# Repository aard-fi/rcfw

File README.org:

* NoTankS Arduino firmware                                            :TOC_4:
  - [[#introduction][Introduction]]
    - [[#working-features][Working features]]
      - [[#general][General]]
      - [[#notanks][NoTankS]]
    - [[#building][Building]]
    - [[#planned-features][Planned features]]
      - [[#general-1][General]]
      - [[#notanks-1][NoTankS]]
    - [[#required-hardware][Required hardware]]
      - [[#flysky-hardware][Flysky hardware]]
      - [[#elrs-hardware][ELRS hardware]]
  - [[#modified-parts][Modified parts]]
  - [[#rc-hardware][RC hardware]]
    - [[#pistol-grip-elrs-transmitter][Pistol grip ELRS transmitter]]
    - [[#elrs-transmitter][ELRS transmitter]]
    - [[#flysky-transmitter][Flysky transmitter]]
    - [[#6-channel-receivers][6 channel receivers]]
  - [[#arduino-shield][Arduino shield]]
  - [[#manual-wiring][Manual wiring]]
    - [[#led-groups][LED groups]]
    - [[#elrs-receiver-reset][ELRS receiver reset]]
    - [[#models][Models]]
      - [[#arctic-tinyrider][Arctic Tinyrider]]
      - [[#notanks-2][NoTanks]]
      - [[#rc-benchy][RC Benchy]]
  - [[#transmitter-channels][Transmitter channels]]
    - [[#default-channel-mapping-for-radiomaster-mt12][Default channel mapping for Radiomaster MT12]]
    - [[#default-channel-mapping-for-radiomaster-pocket][Default channel mapping for Radiomaster Pocket]]
    - [[#default-channel-mapping-for-flysky-fs-i6][Default channel mapping for Flysky FS-i6]]

** Introduction

This is a variant of my [[https://github.com/bwachter/arctic_tinyrider][Arctic Tinyrider controller firmware]], trying to support multiple models (including the original one) with compile time switches:

- the [[https://www.printables.com/model/114300-arctic-tinyrider-rc-snowmobile][Arctic Tinyrider RC snowmobile]]
- the [[https://www.thingiverse.com/thing:2789361][NoTankS tank]]
- the [[https://www.printables.com/model/34128-rc-benchy][RC Benchy]]

It should also work without changes for any model either just using two motors, ore one motor and one servo for steering - the upcoming model specific details are mostly about LED effects.

You can download pre-built firmware for all supported hardware and feature combinations from the [[https://github.com/aard-fi/rcfw/releases][releases page]] and flash them with [[https://github.com/avrdudes/avrdude][avrdude]] (=avrdude -p atmega328p|atmega4809 -c arduino|jtag2updi -P /dev/ttyS0 -b 115200=) , or follow the build instructions below.

Currently supported are the [[https://store.arduino.cc/products/arduino-nano][Arduino Nano]] and the [[https://store.arduino.cc/products/arduino-nano-every][Arduino Nano Every]] as well as all their clones - especially for the Nano I'd recommend getting a cheap clone (ideally with USB-C) via ebay or aliexpress.

The Every uses the first UART via USB serial, and the second UART via the RX/TX pins (which are used for connecting to the receiver). The older Nano connects its first (and only) UART to both USB serial and the RX/TX pins - so it should be programmed with the rest of the circuit powered down.

This is mostly annoying when actively developing - so for models which only occasionally get updated firmware without active development a generic Nano clone should be sufficient, and way cheaper. At the time of writing a Nano clone (which even has USB C) costs less than 1 EUR, while the original Every goes up to 20 EUR, with clones (which also stick to Micro USB for some reason) selling for roughly 12 EUR. Schematics and PCB layout for a shield offering all connections used by this project are in ./arduino-nano-shield/ - and can be [[https://www.pcbway.com/project/shareproject/rcfw_Arduino_Nano_shield_ea388a65.html][ordered via PCBWay]]. See below for build instructions.

The only other disadvantage of the original Nano for basic models is the lower serial port speed of 115200 - but that should not be an issue for the type of model this firmware tries to support. For ELRS receivers you may have to set their serial speed to 115200 once when using a Nano.

*** Working features
The initial version was written for IBUS receivers - some of the advanced features may not work with CRSF receivers yet.

**** General
- ignition switch: throttle is pinned to zero unless ignition switch is on. This allows somewhat safer handling when not fully switched off. A LED connected to D13 will signal throttle state by blinking (off) or solid light (on).
- throttle and steering (obviously)
- reversing, when supported by the model
- control remapping: a three state switch can be used to change controls. Exact functionality depends on model and transmitter used.
- dynamic speed control: a dial can be used to limit the speed without having to change the throttle curve in the transmitter. In the default setting the transmitter starts with 50% output, and can be set up to 100%. Exact functionality depends on model and transmitter used.
- failsafe requires the ability of the receiver to send sane values when connectivity has been lost. This works well with ELRS receivers, untested with Flysky, though it may be possible with some.
- three groups of LEDs can be used for models in the standard configuration: back/power, front and effect. Any of those LED groups can be set to an arbitrary number of pins from 0 to as many pins are available

Ignition switching, control remapping and dynamic speed control currently can be disabled at compile time to free up channels.

Flysky support will mostly be maintained at the current level, while new features target CRSF. Some rely on ELRS/CRSF behaviour, while others could be enabled somewhat easily for flysky as well. CRSF only features are:

- link detection on startup. The main program will only start running once link has been established
- receiver power cycling. With additional wiring (see below) the receiver can be power cycled on startup. This is recommended, as ELRS receivers go into WiFi configuration mode after some time, and would need manual intervention
- link monitoring with board reset after timeout, configurable at compile time
- remote type detection. With the controls for channel 4 in default position the type of remote (stick or pistol grip) can be auto-detected. This is a compile time setting, which defaults to on.

**** NoTankS
- turning based on accelerating or decelerating one side, depending on the current speed. This also allows turning at zero speed
- curves for low speed cutoff to keep the motors cooler

*** Building

Get the [[https://www.arduino.cc/en/software][Arduino IDE]], and the following libraries:

- the [[https://github.com/arduino-libraries/Servo][servo library]]
- for CRSF use [[https://github.com/AlfredoSystems/AlfredoCRSF][AlfredoCRSF]]
- for IBUS use [[https://github.com/bmellink/IBusBM][IBusBM]]

Configure the correct board (Nano or Nano Every are supported, Every recommended), and go through the defines at the beginning of the file to configure the build for your model and transmitter setup.

Alternatively you can install [[https://docs.arduino.cc/arduino-cli/][arduino-cli]], and use the included Makefile: =make deps= once, and then =make all-variants=, or =make= with the flags you want. See the Makefile for more details.

*** Planned features
**** General
- steering curve adjustment for controllers with two potis
- toggling ESC power supply/board power supply

**** NoTankS
- optimising the steering to result in as little speed change as possible

*** Required hardware

- one Arduino Nano Every
- one receiver
- one radio
- two ESCs with reverse which use the first PWM input value to configure the zero position. It also should be configurable for forward/reverse - most come in forward/reverse/brake configuration, and not all allow omitting the brake. I'm using the 160A variant from [[https://www.aliexpress.com/item/1005006256842555.html][here]].

**** Flysky hardware

Recommendation here is the FS-A8S as receiver, and an AFHDS 2a transmitter, like the FS-i6. When starting new I'd recommend going for ELRS hardware instead, though.

The main drawback of the FS-A8S is the lack of a second iBus - so we can't send custom telemetry data back to the radio. On the plus side it is a tiny receiver, very cheap (roughly 10 EUR), and can output up to 18 channels via iBus. I'm not aware of receivers of a similar size with more than one iBus - other small Flysky receivers just have more connectors for PWM breakout cables, which we don't need as we're controlling that part via the Arduino.

**** ELRS hardware

Any ELRS transmitter should do, if you're looking for recommendations:

- for a pistol grip style one, Radiomaster MT12
- for a traditional drone/plane one, Radiomaster Boxer M2, or if you want to be fancier, the TX16S
- for a small, more portable one, Radiomaster Pocket

For receivers any of the compact (nano) receivers should be fine, from any manufacturer - as far as I'm aware all of them have RX/TX ports for CRSF. Some of the larger ones do not have that - but the tiny ones are easier to stuff into models anyway.

Main drawbock of ELRS is that the receivers are roughly double the price of AFHDS ones - but for that we always have the ability to send telemetry back.

** Modified parts
For some of the models I've modified parts. You can find those in separate repositories:

- [[https://github.com/bwachter/arctic_tinyrider][Arctic Tinyrider]]
- [[https://github.com/bwachter/notanks/][NoTankS]]

** RC hardware

Both throttle curve and trim settings will change the values sent by the transmitter. Currently the assumption is that for our models we can adjust those settings on the Arduino, so adjusted input may be improperly handled - don't use that.

*** Pistol grip ELRS transmitter
With the default setup of steering at channel 1 and throttle at channel two basic control will work out of the box.

Remapping of throttle and steering is not supported as it does not make much sense with that style of transmitter.

The ignition switch is expected on channel 9.

*** ELRS transmitter
This setup is currently untested, but should be working.

The ignition switch is expected on channel 5, which should be one of the two-state switches in the default configuration.

*** Flysky transmitter
At least the FS-i6 requires extra setup for the switches, see the transmitter section below for details.

The ignition switch is expected on channel 7.

*** 6 channel receivers

VRB is currently not used, so to make this work you need to select three features to drop to free up channels, and disable them at compile time. With ELRS receivers supporting at least 16 channels, and all the cheap AFHDS nano receivers supporting 10 support for running building with less than 10 channels may be dropped eventually.

** Arduino shield

The included Arduino shield simplifies the wiring a lot - see the next section if you prefer manual wiring.

#+CAPTION: Three PCB versions, left to right V1, V2 and V2.1
[[./files/arduino_shields.jpg]]

If you want the receiver controllable via the Arduino solder a 1kΩ resistor into =R1=, and a  =BD139= or compatible transistor into =Q1=. If you don't need that just bridge pins 1 and 2 of =Q1=.

If you want LEDs solder =2N3904= or compatible transistors into =Q2= and =Q3=, and 4.7kΩ resistors into =R2= and =R3=. If your LEDs are 5V tolerant you can just bridge =R2/R3= instead. Solder pin headers into =J4= and =J5= - each can support two connections.

To prevent the Arduino powering the ESC and motors when only plugged in via USB solder a diode into =D1=. This can be bridged in case you'd rather just be careful, and buy more Arduinos when you mess up.

For the ELRS connector, solder a 4 pin header into =J1=.

For one ESC, solder one 3 pin header into =J2=. This will power the circuit when on battery. For a second ESC, also solder one 3 pin header into =J3=. The power connector from this leads to =J6= - if you want to power extra devices not controlled from the Arduino solder a 6 pin header into that one.

For the servo solder a 3 pin header into =D10=. In case you need two servos, but only one ESC also populate J3, and add a wire bridge from the middle pin of =J3= to the middle pin of =J2= - this will connect the otherwise isolated power pin of =J2/J6=.

To make I²C accessible solder a 3 pin header into =J7=.

The V2 version (included here, but not yet available for order) includes some conveniences for some model:

- the servo header =D10= can be populated with a 3x2 pin header, allowing to plug in two servos. This is useful for the RC benchy to move the steering wheel as well
- a jumper was added between voltage pins of the two ESC headers =J2/J3=. This allows easy power connection for single ESC models, either by jumper or permanent bridge
- a 4 pin header with Arduino pins =D5= and =D6= got added with a common GPS footprint, for use via software serial, though may be useful for extra pins on some other models as well

The V2.1 version adds:

- a three pin header behind the LED resistors over =D11/D12/D13= to allow easy connection of a =74HC595D= module for adding more LEDs
- pin headers on =A20= and =A21= and for future expansions

** Manual wiring

You'll need one power and one ground bar to connect everything to. A quick and dirty variant is getting ready made jumper wires, cut them and then twist end solder the ends together. On the Arduino connect ground and VIN to ground/power bars via a diode to make sure components can't draw power through the Arduino if it is the only thing powered, like during flashing.

The Pins are set up to minimise gaps, soldering three three-pin-headers will cover all pins on one side of the Arduino, while connecting the unused RST pin. On the other side just VIN and D13 need to be populated.

On setups with two or more ESCs make sure to only connect the power pin of one of them.

Nano receivers should have dedicated ground and power connectors either in the header or cable - in that case just connect all of them. For other receivers connect the bus, and take ground and power from any other channel.

The following sections contain tables with the pinouts, with the table colums ordered according to the pinout of the component cables.

IBUS receivers have three pin connectors, and only connect to RX. CRSF receivers have four pin connectors, and also connect to TX. The pinouts are for the Arduino Nano Every - on the Nano use RX/TX instead. Note that flashing on the Nano uses RX/TX, so for that board RX should be disconnected on during flashing.

*** LED groups

The Arduino can tolerate about 20mA per pin, with a total of 200mA. One bright 5mm LED draws roughly 20mA - so three sets of two LEDs should be safe to connect directly. For ad-hoc cabling it is sensible to provide a ground pin to connect to a separate ground bar for additional LEDs. When switching LEDs via a transistor it also makes sense to create a power bar.

With insufficient pins, or more/brighter LEDs they should be wired via a transistor. For a small NPN transistor like the 2N3904 you'd connect the base to the Arduino pin through a 4.7kΩ resistor, emitter to GND, and the LED between VCC and the collector.

The default LED pins are in this table:

|             | Pin 1 | Pin 2 |
|-------------+-------+-------|
| status/back | D13   | D2    |
| front       | D11   | D12   |
| effect      | D4    | D5    |

Pin 2 is only relevant when attaching two power hungry LEDs directly for one specific effect, and may have to be explicitly enabled for a specific model.

If a model doesn't incorporate LEDs one status LED should still be visible for safety reasons. This can either be achieved by mounting the Arduino in a way that the on board LED connected to pin 13 becomes visible, or by connecting an extra LED to pin 13.

When incorporating LEDs into a model the status LEDs should be used as the rear lights.

*** ELRS receiver reset

Pin A7 is configured as digital pin, and pulled high on startup. This allows powering the receiver only when the program is running, and power cycling it as needed.

To use this you'll need a NPN transistor like the BD139. Connect the base to A7 through a 1kΩ resistor, emitter to GND, collector to GND of the receiver, and  of the power in of the receiver to VCC.

*** Models
**** Arctic Tinyrider

|          | GND | 5v | arduino | arduino |
|----------+-----+----+---------+---------|
| ESC      | x   | x  | D3      |         |
| receiver | x   | x  | RX1     | TX1     |
| arduino  | x   | x  |         |         |
| servo    | x   | x  | D10     |         |

**** NoTanks

|           | GND | 5v | arduino | arduino |
|-----------+-----+----+---------+---------|
| left ESC  | x   | x  | D3      |         |
| right ESC | x   | x  | D4      |         |
| receiver  | x   | x  | RX1     | TX1     |
| arduino   | x   | x  |         |         |

**** RC Benchy

|          | GND | 5v | arduino | arduino |
|----------+-----+----+---------+---------|
| ESC      | x   | x  | D3      |         |
| receiver | x   | x  | RX1     | TX1     |
| arduino  | x   | x  |         |         |
| servo    | x   | x  | D10     |         |

** Transmitter channels
This section contains tables about channel setups for all tested transmitters, with information on how to set up additional switches, if needed.

*** Default channel mapping for Radiomaster MT12

| Channel | Trigger  | Type            | Comments                               |
|---------+----------+-----------------+----------------------------------------|
|       1 | wheel    |                 |                                        |
|       2 | throttle |                 |                                        |
|       3 | SA       | switch, 3 state | default 1000                           |
|       4 | SB       | button          | default 1000, starts timer per default |
|       5 | P1       | poti            | default 1500                           |
|       6 | P2       | poti            | default 1500                           |
|       7 | SC       | button, 2 state | default 1000                           |
|       8 | SD       | button, 2 state | default 1000                           |

Note that channel 5 for ELRS is typically a 1 bit channel for arming - and as such the first poti mapped to channel 5 is not ideal. This firmware assumes that it got remapped to channel 5, and the expansion module with the two switches got installed and mapped, leading to the following configuration:

| Channel | Trigger  | Type            | Comments                               |
|---------+----------+-----------------+----------------------------------------|
|       1 | wheel    |                 |                                        |
|       2 | throttle |                 |                                        |
|       3 | SA       | switch, 3 state | default 1000                           |
|       4 | SB       | button          | default 1000, starts timer per default |
|       5 | FL1      | switch, 2 state | default 1000, expansion module (front) |
|       6 | P2       | poti            | default 1500                           |
|       7 | SC       | button, 2 state | default 1000                           |
|       8 | SD       | button, 2 state | default 1000                           |
|       9 | P1       | poti            | default 1500                           |
|      10 | FL2      | switch, 2 state | default 1000, expansion module (back)  |

To configure the expansion module

- go to hardware settings, and set S3/S4 to =switch=
- scroll down, and set =FL1= to =S3=, =FL2= to =S4=, both with =2POS=
- go to model settings, mixes page, and change channel 5 to FL1, add channel 9 with S1, and add channel 10 with FL2

*** Default channel mapping for Radiomaster Pocket

| Channel | Trigger                 | Type            | Comments     |
|---------+-------------------------+-----------------+--------------|
|       1 | right stick, left/right |                 |              |
|       2 | right stick, up/down    |                 |              |
|       3 | left stick, up/down     |                 | default 1000 |
|       4 | left stick, left/right  |                 |              |
|       5 | SA                      | switch, 2 state | default 1000 |
|       6 | SB                      | switch, 3 state | default 1000 |
|       7 | SC                      | switch, 3 state | default 1000 |
|       8 | SD                      | switch, 2 state | default 1000 |
|       9 | SE                      | button, 2 state | default 1000 |
|      10 | SI                      | poti            | default 1000 |

*** Default channel mapping for Flysky FS-i6

| Channel | Trigger                 | Type            | Comments     |
|---------+-------------------------+-----------------+--------------|
|       1 | right stick, left/right |                 |              |
|       2 | right stick, up/down    |                 |              |
|       3 | left stick, up/down     |                 | default 1000 |
|       4 | left stick, left/right  |                 |              |
|       5 | VRA                     | poti            | default 1000 |
|       6 | VRB                     | poti            | default 1000 |
|       7 | SWA                     | switch, 3 state | default 1000 |
|       8 | SWB                     | switch, 2 state | default 1000 |
|       9 | SWC                     | switch, 2 state | default 1000 |
|      10 | SWD                     | switch          | default 1000 |

VRA/VRB are configured on channels 5/6 per default in 'aux channel setup', while the switches are not assigned.

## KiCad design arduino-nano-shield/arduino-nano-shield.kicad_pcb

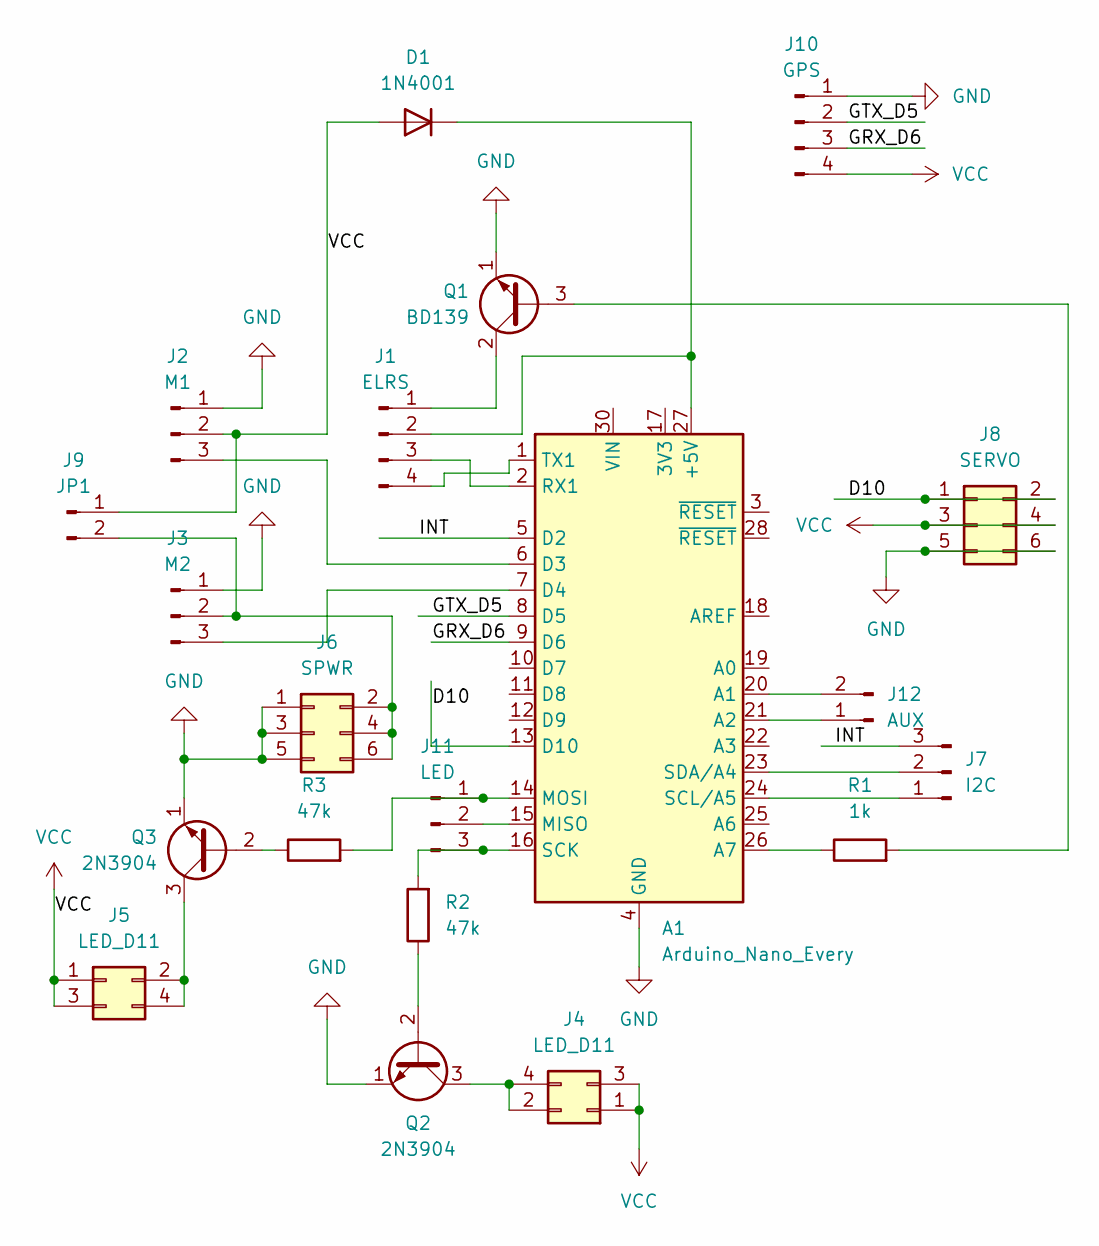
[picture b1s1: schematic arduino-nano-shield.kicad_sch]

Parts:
A1: Arduino_Nano_Every; Arduino_Nano
D1: 1N4001; D_DO-41_SOD81_P10.16mm_Horizontal
J1: ELRS; PinHeader_1x04_P2.54mm_Vertical
J2: M1; PinHeader_1x03_P2.54mm_Vertical
J3: M2; PinHeader_1x03_P2.54mm_Vertical
J4, J5: LED_D11; PinHeader_2x02_P2.54mm_Vertical
J6: SPWR; PinHeader_2x03_P2.54mm_Vertical
J7: I2C; PinHeader_1x03_P2.54mm_Vertical
J8: SERVO; PinHeader_2x03_P2.54mm_Vertical
J9: JP1; PinHeader_1x02_P2.54mm_Vertical
J10: GPS; PinHeader_1x04_P2.54mm_Vertical
J11: LED; PinHeader_1x03_P2.54mm_Vertical
J12: AUX; PinHeader_1x02_P2.54mm_Vertical
Q1: BD139; TO-126-3_Vertical
Q2, Q3: 2N3904; TO-92_Inline
R1: 1k; R_Axial_DIN0207_L6.3mm_D2.5mm_P10.16mm_Horizontal
R2, R3: 47k; R_Axial_DIN0207_L6.3mm_D2.5mm_P10.16mm_Horizontal

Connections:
/D10: A1.13 (D10), J8.1, J8.2
/GRX_D6: A1.9 (D6), J10.3
/GTX_D5: A1.8 (D5), J10.2
/INT: A1.5 (D2), J7.3
GND: A1.4 (GND), A1.29 (GND), J2.1, J3.1, J6.1, J6.3, J6.5, J8.5, J8.6, J10.1, Q1.1 (E), Q2.1 (E), Q3.1 (E)
unnamed: A1.27 (+5V), D1.1 (K), J1.2
unnamed: A1.20 (A1), J12.2
unnamed: A1.21 (A2), J12.1
unnamed: A1.26 (A7), R1.1
unnamed: A1.6 (D3), J2.3
unnamed: A1.7 (D4), J3.3
unnamed: A1.15 (MISO), J11.2
unnamed: A1.14 (MOSI), J11.1, R3.2
unnamed: A1.2 (RX1), J1.3
unnamed: A1.16 (SCK), J11.3, R2.2
unnamed: A1.24 (SCL/A5), J7.1
unnamed: A1.23 (SDA/A4), J7.2
unnamed: A1.1 (TX1), J1.4
unnamed: J1.1, Q1.2 (C)
unnamed: J3.2, J6.2, J6.4, J6.6, J9.2
unnamed: J4.2, J4.4, Q2.3 (C)
unnamed: J5.2, J5.4, Q3.3 (C)
unnamed: Q1.3 (B), R1.2
unnamed: Q2.2 (B), R2.1
unnamed: Q3.2 (B), R3.1
VCC: D1.2 (A), J2.2, J4.1, J4.3, J5.1, J5.3, J8.3, J8.4, J9.1, J10.4

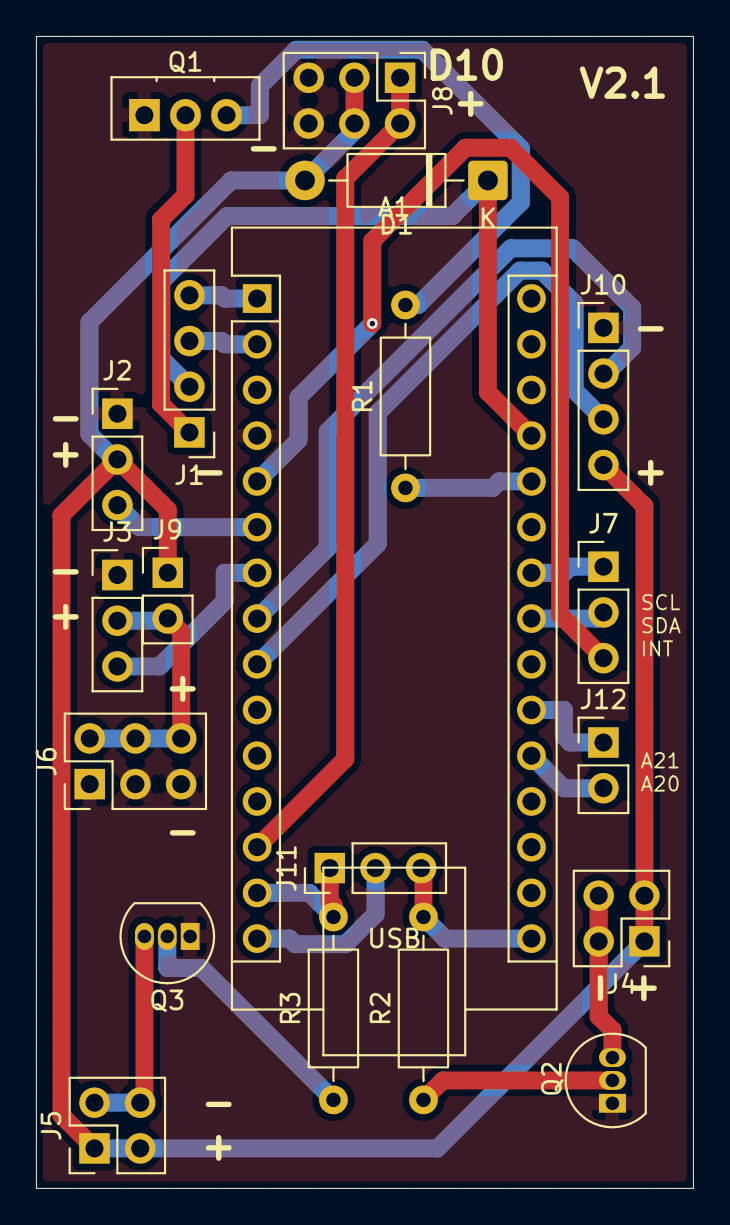
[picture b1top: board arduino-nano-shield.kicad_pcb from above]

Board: 2 copper layers, 36.5 x 64.0 mm, 20 parts (0 on the bottom side), 26 nets.

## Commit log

2025-07-16 refactor: prepare for supporting various models from one firmware
2025-07-16 Log ignition status
2025-07-16 refactor: Add support for multiple RC models
    Introduced support for controlling different RC models
    by defining model-specific configurations and behaviors in the
    rcfw.ino file. The code now uses preprocessor directives to
    switch between configurations for NOTANK and RC_BENCHY models.
    For the NOTANK model, added separate steering controls for
    left and right motor pins, including a new steering logic
2025-07-16 feat: Add conditional debug output based on board type
    This commit introduces conditional debug output functionality based on
    the type of board the code is being compiled for, enhancing flexibility
    and maintainability:
    - Added preprocessor directives to define debug output functions
    (`debug_print` and `debug_println`) that either map to `Serial.print`
    and `Serial.println` or do nothing, depending on the board type.
2025-07-16 refactor: Add support for snow mobile RC model
    Added a new RC model configuration for a snow mobile. This includes
    setting specific motor and servo pins. Defined arrays for front and
    effect LEDs, ensuring compatibility with the current setup. Updated
    steering and motor control logic in `setup` and `controls` to handle
    the snow mobile model. Adjusted `setup_controls` function to correctly
    map throttle and steering channels. Each configuration comes with a
2025-07-16 feat: Add CRSF protocol support in control logic
    This commit adds support for the CRSF protocol in the control
    logic of the "rcfw.ino" file. The code now conditionally includes
    either the IBusBM or AlfredoCRSF library based on the SERIAL_PROTOCOL
    define.
    Changes include:
    - Added new `#define` for CRSF and conditional logic to switch
2025-07-16 docs: Expand hardware and model support in README
    The README has been updated to provide clearer guidance on supported
    models and hardware. Sections on Flysky and ELRS hardware have been
    added under 'Required hardware.' This update introduces the developer's
    attempt to support multiple models including the Arctic Tinyrider,
    NoTankS tank, and RC Benchy with compile-time switches. The hardware
    list now differentiates between Flysky and ELRS hardware with
2025-07-17 docs: Update README with new wiring and setup details
    Expanded README to include more comprehensive wiring and setup
    instructions for different models supported by the NoTankS Arduino
    firmware. Detailed pinout tables have been added for Arctic Tinyrider,
    NoTanks, and RC Benchy, along with information on how to support
    LEDs in future updates. Clarified transmitter setup and the
    configurations necessary for different types of transmitters,
2025-07-17 refactor: Define constants for RX boundary values
    The commit refactors the code by replacing hardcoded RX boundary values
    such as 1000, 1500, and 2000 with defined constants RX_MIN, RX_MID,
    and RX_MAX. This improves readability and maintainability.
    - Introduced a new constant RX_TOLERANCE to handle slight deviations
    from RX_MIN and RX_MAX, improving stability in signal handling.
    - Renamed the function printChannels to print_channels to follow
2025-07-18 refactor: Enhance transmitter type configuration
    Implemented refactor of the transmitter configuration logic to support
    different types of transmitters consistently, including FlySky and
    Radiomaster models in both pistol grip and stick styles. This update
    organizes the code to define the transmitter type (`TX_TYPE`) and
    selects appropriate channel mappings, ensuring correct communication
    protocols (i.e., IBUS or CRSF).
2025-07-18 docs: Update README with building and transmitter info
    Added detailed instructions for building the project using the
    Arduino IDE, including necessary libraries and board configuration.
    Modified the section on RC hardware to replace 'Transmitter setup,'
    with instructions for configuring transmitter channels. Detailed
    channel mappings were introduced for Radiomaster MT12, Radiomaster
    Pocket, and Flysky FS-i6. This update aims to provide clearer
2025-07-18 fix: Add adjustable debug state to reduce log frequency
    Introduced `DEBUG_DELAY` to manage the frequency of debug messages.
    The debug state variable `debug_state` is incremented in each loop
    iteration.
    ```cpp
    //...
    int debug_state = 0;
2025-07-18 feat: Adjust control configuration for improved handling
    Updated the definition of SPEED_CHANNEL for RADIOMASTER_PG to use
    channel 6 instead of 5, as channel 5 issues were causing it to
    act like a switch rather than a potentiometer, affecting control
    precision.
    Enhanced the `controls` function across multiple models (`NOTANK`,
    `RC_BENCHY`, `SNOW_MOBILE`) to accept an additional parameter
2025-07-19 feat: Implement power cycling and watchdog for stability
    This commit introduces power cycling the receiver via a new POWER_PIN
    defined as A7. This allows for easier switching of controllers without
    manual intervention, particularly with ELRS receivers and bind phrases.
    Additionally, a watchdog timer (WDT) is enabled to reset the Arduino in
    case the system becomes unresponsive, enhancing stability.
    For the TX_CRSF protocol, a new LINK_DOWN_DELAY is introduced. The loop
2025-07-22 fix: Correct channel mapping configuration
    Update README.org to clarify channel configuration for ELRS,
    ensuring accurate potentiometer and switch mappings. Specifically,
    describe the correct setup for Radiomaster units including expansion
    modules, correcting the previous misconfiguration of channel 5.
    In rcfw.ino, fix the IGNITION_CHANNEL definition for Radiomaster
    transmitters by combining conditions for RADIOMASTER_ST and
2025-07-22 refactor: Simplify transmitter channel handling
    Refactor transmitter channel handling by introducing a new struct
    'channel_mapping' to encapsulate related channel information, and
    streamline channel configuration for different types of transmitters.
    Replace individual channel defines with a mapping function to obtain
    a default or specific transmitter's channel setup. This reduces
    repetitive logic and allows for cleaner and more maintainable code.
2025-07-22 refactor: Adjust channel mapping to align with transmitter numbers**
    The commit updates the `flysky_st_mapping` to increase each channel by one,
    aligning with the displayed transmitter numbers for improved clarity.
    Consequently, adjustments are made in `setup_controls()` and `loop()`
    functions, reducing the transmitted channel index by one when using
    the IBus protocol. This change ensures consistency across channel
    mappings and simplifies channel handling logic, minimizing the need
2025-07-22 feat: Enhance transmitter type detection
    Changed the TX_TYPE definition to RADIOMASTER, enhancing flexibility
    in distinguishing between different transmitter models. Implemented
    runtime detection for remote control types by examining channel 4's
    value during setup. This change determines which transmitter is
    connected and sets the `current_tx` variable accordingly. A debug
    output was added to assist in verifying the active transmitter,
2025-07-22 refactor: Support variable-length LED arrays
    Modified the LED handling to accommodate variable-length LED arrays
    by introducing an end-of-array marker, -1. This allows for flexibility
    in different model configurations. Updated the LED definitions by
    adding -1 as an end marker.
    Refactored the set_led function to iterate over the LED array until
    the end marker is encountered. This enhances usability for models
2025-07-22 refactor: Remove unused failsafe code
    Remove the unused failsafe_channel declaration and related
    conditional failsafe code in the loop function. These elements
    were not being utilized in the current implementation for either
    IBus or CRSF protocols, making this code redundant.
    Originally this was part of an attempt at implementing a failsafe for
    receivers not properly supporting it - but never quite worked. ELRS
2025-07-27 fix: Address power pin and LED handling issues
    This commit resolves issues with power pin definitions and LED
    handling during setup and CRSF transmitter initialization. Key
    changes include:
    1. **Power Pin Definitions**:
    - Added a new `POWER_PIN_RCV` for enhanced control.
    - Changed `POWER_PIN` from `A7` to `A6`.
2025-07-28 fix: Adjust LED initialization and control behavior
    Refactor LED array management and correct LED control behavior in
    initialization phase. The `POWER_LEDS` and `FRONT_LEDS` definitions have
    been modified to improve clarity and correct assignments appropriate to
    the `NOTANK` model condition. The redundant incrementation of the index
    variable `i` has been removed and consolidated within loops in `set_led`
    and `setup_led`.
2025-08-17 feat: Support multiple UART speeds for Nano boards
    Updated README to clarify the differences between the Arduino
    Nano Every and the original Nano, highlighting their UART
    capabilities and price differences. The original Nano now has
    automatic UART speed adjustments with CRSF_SPEED set to 115200
    and other boards retaining 420000 as default for reliability.
    In rcfw.ino, added a preprocessor directive to set CRSF_SPEED
2025-08-17 docs: Revise README for LED and receiver configurations
    Reorganized and expanded the README to include clear sections and
    instructions related to LED groups and ELRS receiver reset, clarifying
    wiring details and use cases.
    - Added separate sections for LED groups and ELRS receiver reset
    - Updated descriptions for default LED pins and configurations
    - Emphasized the importance of visible status LEDs for safety
2025-08-17 fix: Correct typo in throttle_channel initialization
    Corrected a typo in the `throttle_channel` variable initialization
    within the `setup_controls` function. The previous code incorrectly
    spelled it as `throttle_thannel`. This typo could cause runtime
    errors or unexpected behavior during control setup. By fixing
    the typo, we ensure `throttle_channel` is properly assigned
    when `controls` is set to `RX_MAX`.
2026-06-04 Add Arduino shield schematics and documentation
2026-06-04 Add V2 board
    - jumper for powering second ESC header VCC from main VCC net
    - GPS header with D5/D6
    - support two servos on servo header
2026-06-08 Add v2.1 board
    - add three pin header as alternative for LED connections (populate
    with angled header) to connect to various multiplexing controllers
    - add headers for A20 and A21 as aux connectors
2026-06-11 Add support for LED multiplexing via 74HC595D
2026-06-11 Add Makefile for building, using arduino-cli
2026-06-11 Fix build for Flysky remotes
2026-06-12 Move matrix builds to Makefile, and add gh action
2026-06-12 add missing checkout in release action
